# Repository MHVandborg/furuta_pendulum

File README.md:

# Furuta Pendulum

A Furuta (rotary inverted) pendulum system controlled by a neural network running on a custom PCB.

The system consists of a horizontal rotating arm driven by a BLDC motor, with a freely swinging pendulum attached at the end. The neural network controller learns to swing up and balance the pendulum using reinforcement learning trained in a physics simulation, then deployed directly onto the MCU.

## End Goal — Double Furuta Pendulum

The ultimate goal is a **double Furuta pendulum**: motorised arm → first free pendulum → second free pendulum, all balanced simultaneously in the inverted position by a single neural network. The current hardware (PCB rev1) targets the single pendulum first as a validated stepping stone. Double Furuta requires a PCB rev2 with a third encoder.

---

## Control Architecture

### Single Furuta (PCB rev1 — current)

```
[AS5600 arm]  [AS5600 pendulum 1]
      |               |
      +-------+-------+
              |
        [Neural Network]  MLP 2×64, trained with PPO
        inputs:  θ_arm, θ_p1, ω_arm, ω_p1
        output:  torque_command (−1…+1)
              |
        [SimpleFOC / DRV8313]
              |
        [GBM2804H-100T BLDC]
```

### Double Furuta (PCB rev2 — future)

```
[AS5600 arm]  [AS5600 pendulum 1]  [AS5600 pendulum 2]
      |               |                    |
      +-----------+---+--------------------+
                  |
            [Neural Network]  MLP 2×64 (extended inputs), trained with SAC
            inputs:  θ_arm, θ_p1, θ_p2, ω_arm, ω_p1, ω_p2
            output:  torque_command (−1…+1)
                  |
            [SimpleFOC / DRV8313]
                  |
            [GBM2804H-100T BLDC]
```

A single NN handles both swing-up and balancing via curriculum learning — it trains near vertical first, then faces progressively larger starting angles.

---

## Repository Structure

```
furuta_pendulum/
├── firmware/          # Bare-metal C (ARM GCC, CMake) → firmware/README.md
├── hardware/
│   ├── pcb/           # KiCad schematic + layout → hardware/pcb/COMPONENTS.md
│   └── mechanical/    # Fusion 360 3D design files
├── neural_network/    # RL training + Gymnasium env + exported weights → neural_network/README.md
├── bootloader/        # UF2 bootloader binary for ATSAMD51J20A
└── docs/              # Datasheets and reference documents
```

---

## Toolchain

| Area | Tools |
|---|---|
| Firmware | ARM GCC, CMake, VS Code, Atmel-ICE + Tag-Connect TC2030 (SWD), UF2 bootloader |
| ML / Training | Python, TensorFlow / Keras, Gymnasium, PPO → SAC |
| Inference on MCU | TensorFlow Lite Micro (TFLM) |
| Mechanical | Fusion 360, PLA (FDM) |
| PCB | KiCad |

---

## PCB Revision History

| Rev | Tag | Date | Notes |
|-----|-----|------|-------|
| 1 | [`hw-rev1`](../../releases/tag/hw-rev1) | 2026-06-07 | First production run — JLCPCB. Single Furuta (2 encoders) |
| 2 | *(planned)* | TBD | Add AS5600 #3 + third I2C bus for double Furuta |

---

## Further Reading

| Document | Contents |
|---|---|
| [ROADMAP.md](ROADMAP.md) | Full phased development plan with checklists |
| [hardware/pcb/COMPONENTS.md](hardware/pcb/COMPONENTS.md) | Component choices, rationale, and PCB design decisions |
| [firmware/README.md](firmware/README.md) | Firmware architecture, build instructions, peripheral map |
| [neural_network/README.md](neural_network/README.md) | RL training approach, simulation, reward design, export pipeline |

---

## Contact

If you use or build on this project, I'd love to hear about it! Feel free to open an issue or reach out directly.

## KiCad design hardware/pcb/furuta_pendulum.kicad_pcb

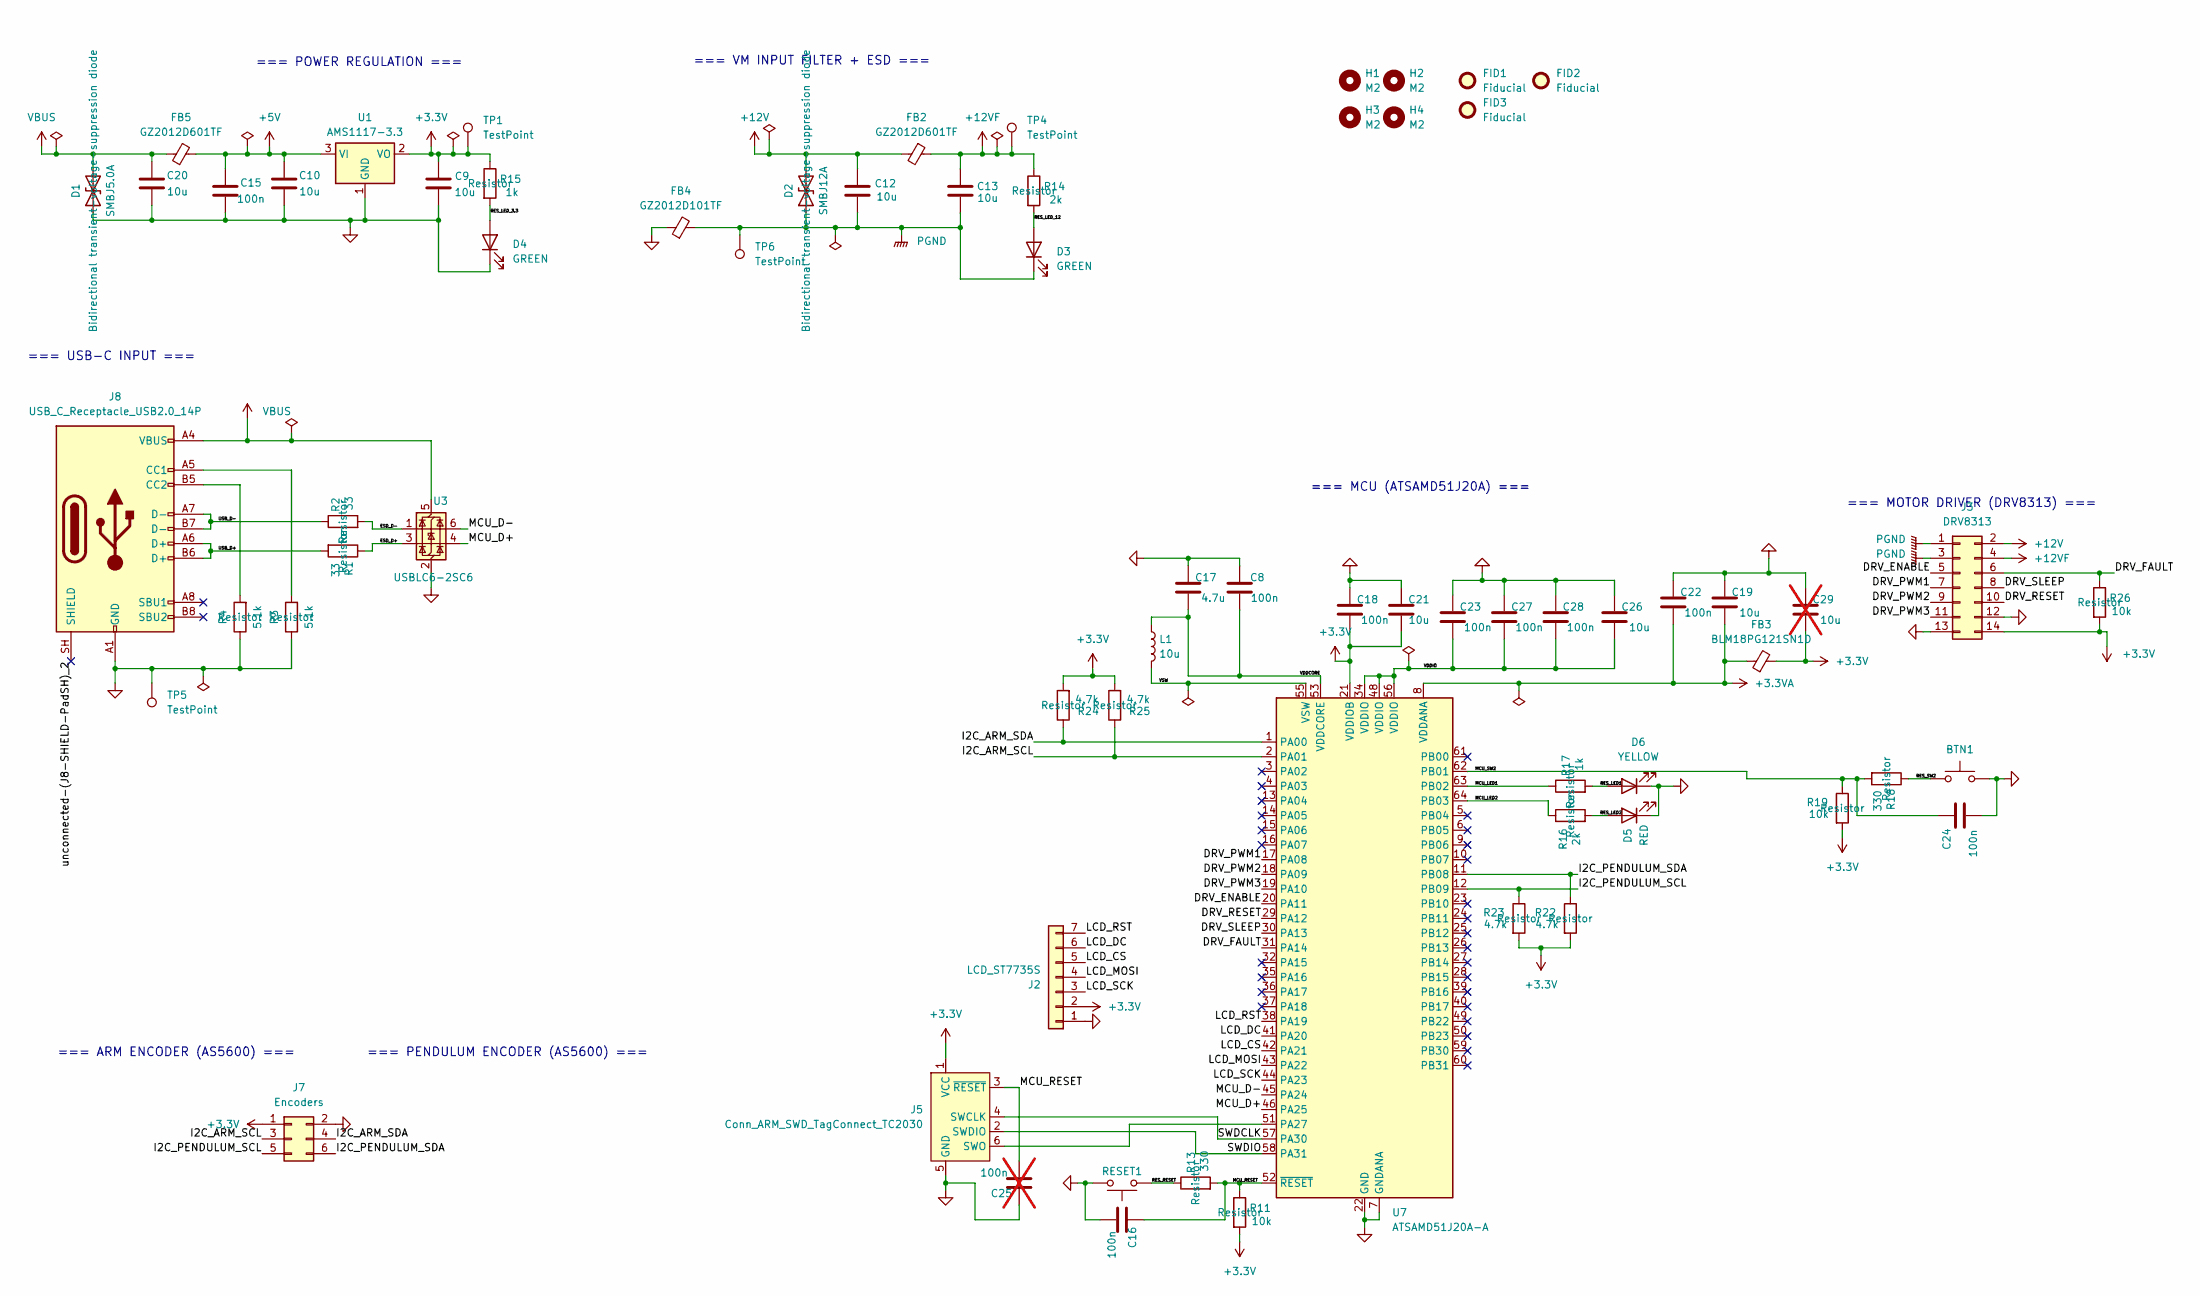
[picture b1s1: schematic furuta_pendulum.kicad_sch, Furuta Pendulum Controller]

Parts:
BTN1: TS-1088-AR02016; SW_TS-1088-AR02016; LCSC Part # C720477
C8, C15, C16, C18, C22, C23, C24, C27, C28: 100n; C_0402_1005Metric; LCSC Part # C1525
C9, C10, C12, C13, C19, C20, C21, C26: 10u; C_0805_2012Metric; LCSC Part # C440198
C17: 4.7u; C_0603_1608Metric; LCSC Part # C19666
C25: 100n; C_0402_1005Metric; LCSC Part # C1525; not fitted
C29: 10u; C_0805_2012Metric; LCSC Part # C440198; not fitted
D1: SMBJ5.0A; D_SMB
D2: SMBJ12A; D_SMB
D3, D4: GREEN; LED_0805_2012Metric; LCSC Part # C2297
D5: RED; LED_0603_1608Metric; LCSC Part # KT-0603R
D6: YELLOW; LED_0805_2012Metric; LCSC Part # KT-0805Y
FB2, FB5: GZ2012D601TF; L_0805_2012Metric; LCSC Part # C1017
FB3: BLM18PG121SN1D; L_0603_1608Metric; LCSC Part # C14709
FB4: GZ2012D101TF; L_0805_2012Metric; LCSC Part # C1015
FID1, FID2, FID3: Fiducial; Fiducial_1mm_Mask2mm
H1, H2, H3, H4: M2; MountingHole_2.2mm_M2
J2: LCD_ST7735S; PinHeader_1x07_P2.54mm_Vertical
J3: DRV8313; PinHeader_2x07_P2.54mm_Vertical
J5: Conn_ARM_SWD_TagConnect_TC2030; Tag-Connect_TC2030-IDC-FP_2x03_P1.27mm_Vertical
J7: Encoders; PinHeader_1x06_P2.54mm_Vertical
J8: USB_C_Receptacle_USB2.0_14P; USB_C_Receptacle_HRO_TYPE-C-31-M-12
L1: 10u; L_0603_1608Metric; LCSC Part # C1035
R1, R2: 33; R_0402_1005Metric; LCSC Part # C25105
R3, R4: 5.1k; R_0402_1005Metric; LCSC Part # C25905
R11, R19, R26: 10k; R_0402_1005Metric; LCSC Part # C25744
R13, R18: 330; R_0402_1005Metric; LCSC Part # C25104
R14, R16: 2k; R_0402_1005Metric; LCSC Part # C4109
R15, R17: 1k; R_0402_1005Metric; LCSC Part # C11702
R22, R23, R24, R25: 4.7k; R_0402_1005Metric; LCSC Part # C25900
RESET1: TS-1088-AR02016; SW_TS-1088-AR02016; LCSC Part # C720477
TP1, TP4, TP5, TP6: TestPoint; TestPoint_Pad_D1.5mm
U1: AMS1117-3.3; SOT-223-3_TabPin2; LCSC Part # C6186
U3: USBLC6-2SC6; SOT-23-6
U7: ATSAMD51J20A-A; TQFP-64_10x10mm_P0.5mm

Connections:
+3.3V: C9.1, C18.2, C21.2, C29.2, FB3.2, J2.2, J3.14, J5.1 (VCC), J7.1, R11.2, R15.1, R19.2, R22.2, R23.2, R24.2, R25.2, R26.2, TP1.1 (1_1), U1.2 (VO), U7.21 (VDDIOB)
+3.3VA: C19.2, C22.2, FB3.1, U7.8 (VDDANA)
+5V: C10.1, C15.1, FB5.2, U1.3 (VI)
+12V: C12.1, D2.2 (A2), FB2.2, J3.2
+12VF: C13.1, FB2.1, J3.4, R14.1, TP4.1 (1_1)
/DRV_ENABLE: J3.5, U7.20 (PA11)
/DRV_FAULT: J3.6, R26.1, U7.31 (PA14)
/DRV_PWM1: J3.7, U7.17 (PA08)
/DRV_PWM2: J3.9, U7.18 (PA09)
/DRV_PWM3: J3.11, U7.19 (PA10)
/DRV_RESET: J3.10, U7.29 (PA12)
/DRV_SLEEP: J3.8, U7.30 (PA13)
/ESD_D+: R1.1, U3.3 (I/O2)
/ESD_D-: R2.2, U3.1 (I/O1)
/I2C_ARM_SCL: J7.3, R25.1, U7.2 (PA01)
/I2C_ARM_SDA: J7.4, R24.1, U7.1 (PA00)
/I2C_PENDULUM_SCL: J7.5, R23.1, U7.12 (PB09)
/I2C_PENDULUM_SDA: J7.6, R22.1, U7.11 (PB08)
/LCD_CS: J2.5, U7.42 (PA21)
/LCD_DC: J2.6, U7.41 (PA20)
/LCD_MOSI: J2.4, U7.43 (PA22)
/LCD_RST: J2.7, U7.38 (PA19)
/LCD_SCK: J2.3, U7.44 (PA23)
/MCU_D+: U3.4 (I/O2), U7.46 (PA25)
/MCU_D-: U3.6 (I/O1), U7.45 (PA24)
/MCU_LED1: R17.1, U7.63 (PB02)
/MCU_LED2: R16.1, U7.64 (PB03)
/MCU_RESET: C16.1, C25.2, J5.3 (~RESET), R11.1, R13.2, U7.52 (~RESET)
/MCU_SW2: C24.1, R18.2, R19.1, U7.62 (PB01)
/RES_LED1: D6.2 (A), R17.2
/RES_LED2: D5.2 (A), R16.2
/RES_LED_3.3: D4.2 (A), R15.2
/RES_LED_12: D3.2 (A), R14.2
/RES_RESET: R13.1, RESET1.1 (A), RESET1.2 (A)
/RES_SW2: BTN1.1 (A), BTN1.2 (A), R18.1
/SWDCLK: J5.4 (SWCLK), U7.57 (PA30)
/SWDIO: J5.2 (SWDIO), U7.58 (PA31)
/USB_D+: J8.A6 (D+), J8.B6 (D+), R1.2
/USB_D-: J8.A7 (D-), J8.B7 (D-), R2.1
/VDDCORE: C8.2, C17.2, L1.1, U7.53 (VDDCORE)
/VDDIO: C23.2, C26.2, C27.2, C28.2, U7.34 (VDDIO), U7.48 (VDDIO), U7.56 (VDDIO)
/VSW: L1.2, U7.55 (VSW)
/unconnected-(J8-SHIELD-PadSH)_2: J8.SH (SHIELD)
/unconnected-(J8-SHIELD-PadSH)_2_1: J8.SH (SHIELD)
/unconnected-(J8-SHIELD-PadSH)_2_2: J8.SH (SHIELD)
/unconnected-(J8-SHIELD-PadSH)_2_3: J8.SH (SHIELD)
GND: BTN1.3 (B), BTN1.4 (B), C8.1, C9.2, C10.2, C15.2, C16.2, C17.1, C18.1, C19.1, C20.2, C21.1, C22.1, C23.1, C24.2, C25.1, C26.1, C27.1, C28.1, C29.1, D1.1 (A1), D4.1 (K), D5.1 (K), D6.1 (K), FB4.1, J2.1, J3.12, J3.13, J5.5 (GND), J7.2, J8.A1 (GND), J8.A12 (GND), J8.B1 (GND), J8.B12 (GND), R3.1, R4.1, RESET1.3 (B), RESET1.4 (B), TP5.1 (1_1), U1.1 (GND), U3.2 (GND), U7.7 (GNDANA), U7.22 (GND), U7.33 (GND), U7.47 (GND), U7.54 (GND)
unnamed: J5.6 (SWO), U7.51 (PA27)
unnamed: J8.A5 (CC1), R3.2
unnamed: J8.B5 (CC2), R4.2
PGND: C12.2, C13.2, D2.1 (A1), D3.1 (K), FB4.2, J3.1, J3.3, TP6.1 (1_1)
VBUS: C20.1, D1.2 (A2), FB5.1, J8.A4 (VBUS), J8.A9 (VBUS), J8.B4 (VBUS), J8.B9 (VBUS), U3.5 (VBUS)

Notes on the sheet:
=== POWER REGULATION ===
=== USB-C INPUT ===
=== MCU (ATSAMD51J20A) ===
=== MOTOR DRIVER (DRV8313) ===
=== ARM ENCODER (AS5600) ===
=== PENDULUM ENCODER (AS5600) ===
=== VM INPUT FILTER + ESD ===

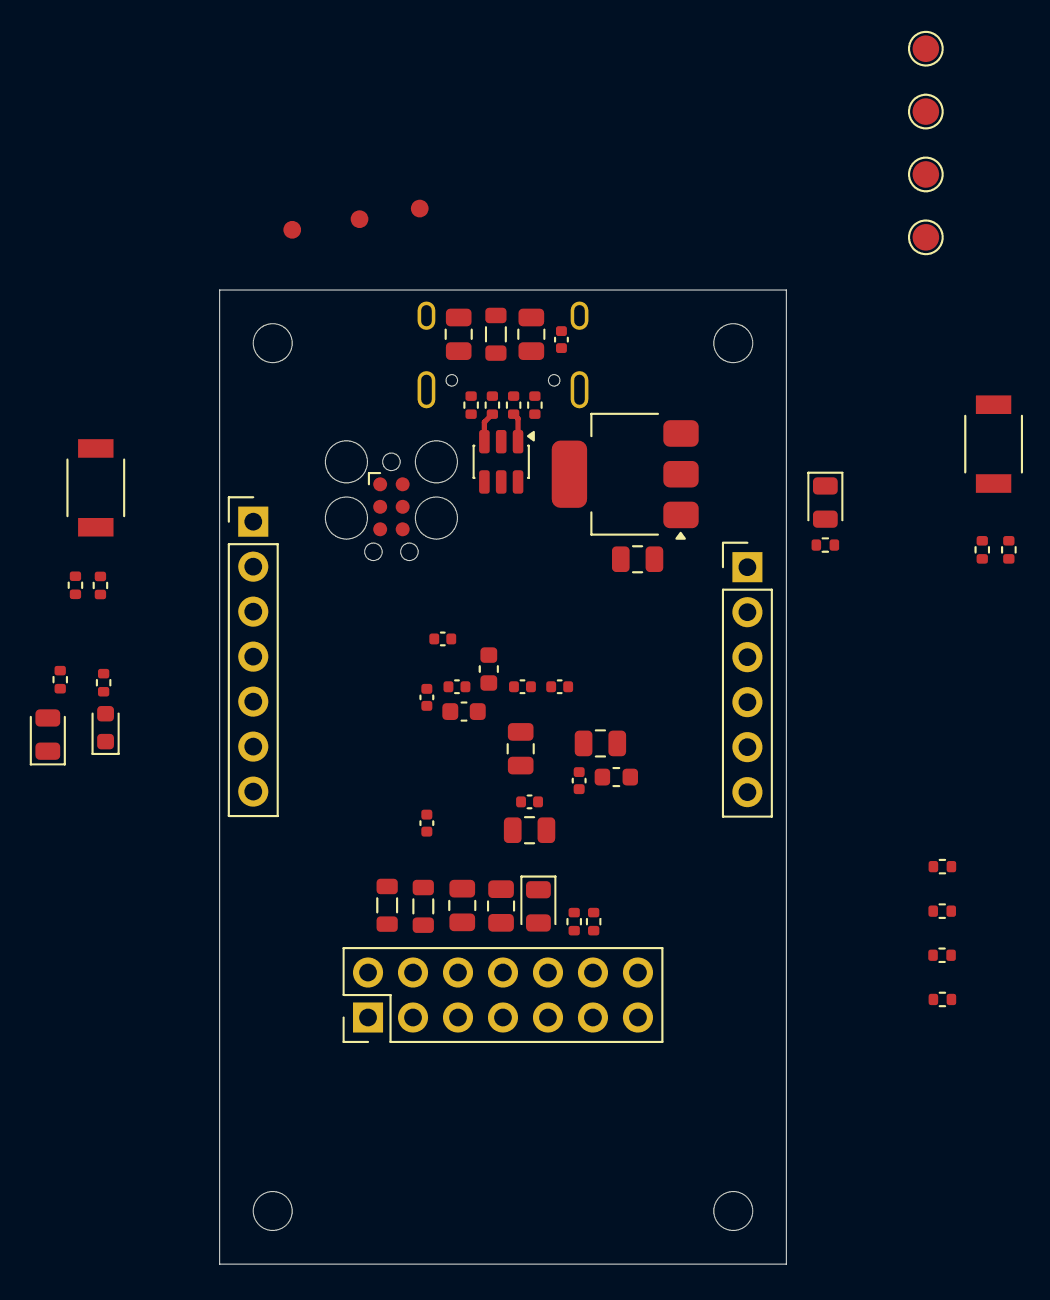
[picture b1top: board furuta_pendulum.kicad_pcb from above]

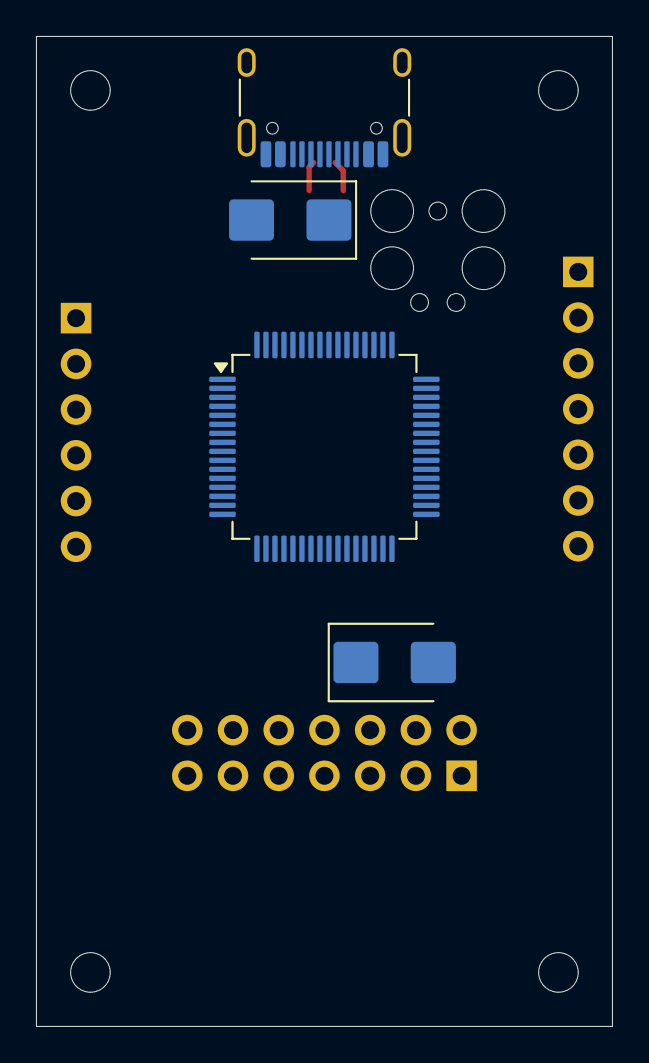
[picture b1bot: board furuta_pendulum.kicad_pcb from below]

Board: 4 copper layers, 32.0 x 55.0 mm, 67 parts (4 on the bottom side), 48 nets.

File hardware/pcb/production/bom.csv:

Comment,Designator,Footprint,LCSC Part Number
TS-1088-AR02016,"BTN1,RESET1",SW_TS-1088-AR02016,C720477
10u,"C10,C12,C13,C19,C20,C21,C26,C9",0805,C440198
100n,"C15,C16,C18,C22,C23,C24,C25,C8",0402,C1525
4.7u,C17,0603,C19666
SMBJ5.0A,D1,D_SMB,
SMBJ12A,D2,D_SMB,
GREEN,"D3,D4",0805,C2297
RED,D5,0603,KT-0603R
YELLOW,D6,0805,KT-0805Y
GZ2012D601TF,"FB2,FB5",0805,C1017
BLM18PG121SN1D,FB3,0603,C14709
GZ2012D101TF,FB4,0805,C1015
LCD_ST7735S,J2,PinHeader_1x07_P2.54mm_Vertical,
DRV8313,J3,PinHeader_2x07_P2.54mm_Vertical,
Encoders,J7,PinHeader_1x06_P2.54mm_Vertical,
USB_C_Receptacle_USB2.0_14P,J8,USB_C_Receptacle_HRO_TYPE-C-31-M-12,
10u,L1,0603,C1035
33,"R1,R2",0402,C25105
10k,"R11,R19,R26",0402,C25744
330,"R13,R18",0402,C25104
2k,"R14,R16",0402,C4109
1k,"R15,R17",0402,C11702
4.7k,"R22,R23,R24,R25",0402,C25900
5.1k,"R3,R4",0402,C25905
TestPoint,"TP1,TP10,TP11,TP4,TP5,TP7,TP8,TP9",TestPoint_Pad_D1.5mm,
AMS1117-3.3,U1,SOT-223-3_TabPin2,C6186
USBLC6-2SC6,U3,SOT-23-6,
ATSAMD51J20A-A,U7,TQFP-64_10x10mm_P0.5mm,

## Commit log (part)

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2026-06-29 updated to detailed project structure
